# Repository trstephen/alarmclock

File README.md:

# alarmclock
### What is CENG 299?
CENG 299 is a second year project course at the University of Victoria. Students execute the full design cycle to create an alarm clock with mp3 audio playback capabilities. A [STM32F407VG](http://www.st.com/web/catalog/mmc/FM141/SC1169/SS1577/LN11/PF252140) microcontroller is responsible for handling I/O, decoding the mp3 and generating the audio output. A custom-designed PCB filters and amplifies the audio output from the STM and contains the circuitry for driving the 7-segment display and cleaning up button input.

### What's in the repo?
**Schematics**

Detail the four main components of the circuit design:
* I/O
* Audio amplification and filtering
* External button connections
* 7-Segment display controller

The files will open natively in  [KiCad](http://www.kicad-pcb.org/display/KICAD/KiCad+EDA+Software+Suite).

Printable schematics, with some helpful notes, are [here](kicad/schematic.pdf).

*TODO*: Include files for the PCB.

**Code**

A skeleton was provided that handles the USB On-The-Go communication and audio decoding. The bulk of the project code is in:
```
main.c
state_machine.c
buttons.c
clock_display.c
```
The included `.coproj` file will open the project in [CoIDE](http://www.coocox.org/software/coide.php) but the project should work wherever the [GCC-ARM](https://launchpad.net/gcc-arm-embedded) compiler is used.

**Known Issues**

* mp3 playback
  * Only works with 128kb/s encoding
  * Stops playback after ~2min and needs to be hard reset before playback can continue

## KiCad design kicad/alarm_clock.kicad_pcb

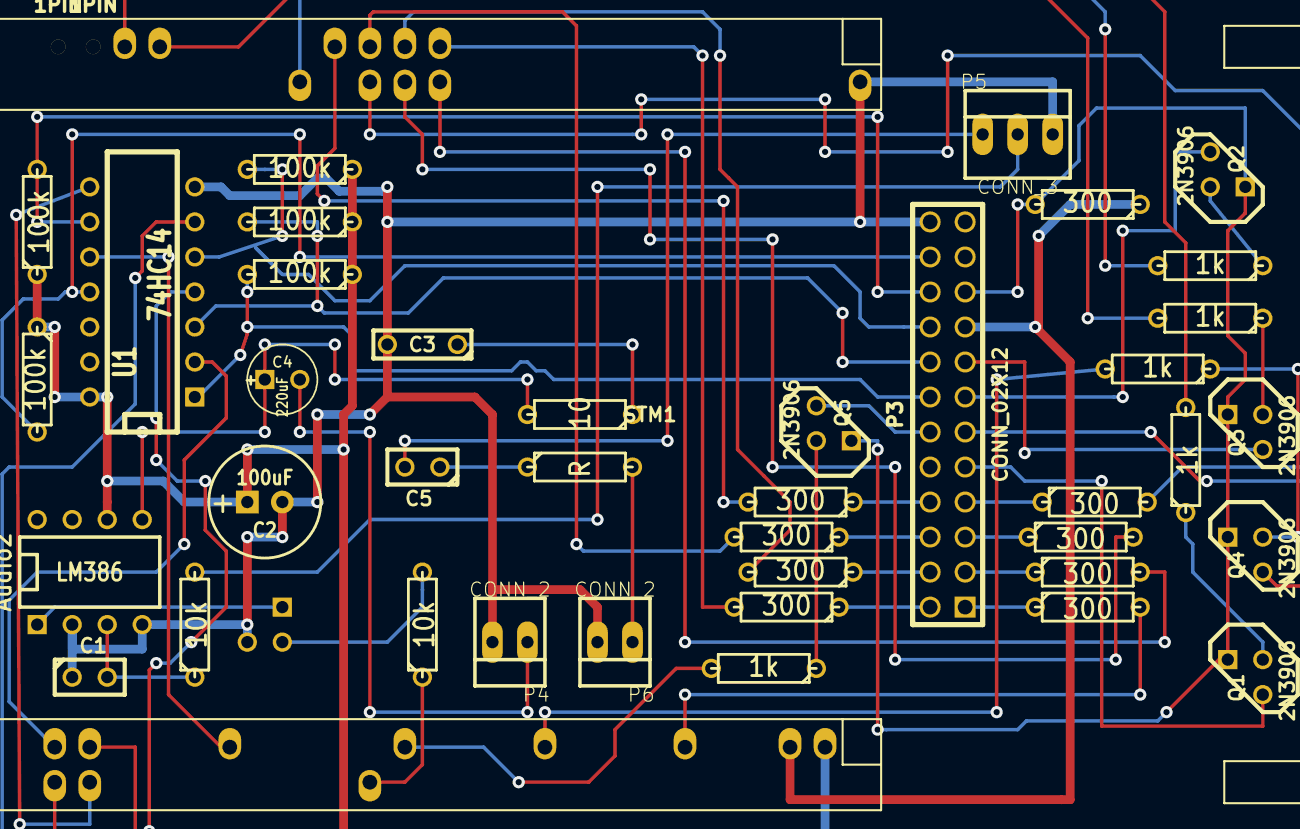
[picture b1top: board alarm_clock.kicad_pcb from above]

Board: 2 copper layers, 43 parts (1 on the bottom side), 56 nets.

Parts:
1PIN, 1PIN#2: P***; 1pin
Audio2: LM386; DIP-8__300
C1: 800pF; C1
C2: 100uF; C1V8
C3: .047uF; C2
C4: 220uF; C1V5
C5: 0.01uF; C1
M1: 2N7000; TO92DGS
P3: CONN_02X12; pin_array_12x2
P4, P6: CONN_2; PINHEAD1-2
P5: CONN_3; PINHEAD1-3
Q1, Q2, Q3, Q4, Q5: 2N3906; TO92-CBE
R1, R2, R4, R5, R6, R7, R8, R9, R10: 300; R3
R3, R20, R21, R22, R23: 1k; R3
R11, R12: 10k; R3
R13: 10; R3
R14, R15, R16, R17, R18: 100k; R3
R19: R; R3
STM1: STM32_F4_DISCOVERY; STM32F4DISC
U1: 74HC14; DIP-14__300

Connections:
3V_205: P3.17, R8.1, STM1.2-5
5V_203: Audio2.6, C2.1, R14.1, R15.1, R16.1, R17.1, R18.1, STM1.2-3, U1.14
AudioIn: C5.1, R19.1
AudioJackGrnd: Audio2.2, Audio2.4, C1.1, C2.2, C3.2, M1.S, P3.24, P4.2, P5.3, P6.2, STM1.1-2, U1.7
AudiojackOut: P6.1, R19.2
DIG_COLON: P3.15, Q3.C
DIG_H01: P3.13, Q2.C
DIG_H10: P3.9, Q1.C
DIG_M01: P3.12, Q5.C
DIG_M10: P3.11, Q4.C
unnamed: Q2.B, R20.1
unnamed: Q5.B, R23.1
unnamed: Q1.B, R3.1
unnamed: Q4.B, R22.1
unnamed: Q3.B, R21.1
unnamed: C3.1, R13.1
unnamed: Audio2.5, C4.1, R13.2
unnamed: M1.G, R12.2
unnamed: Audio2.3, C1.2, R11.1
unnamed: Audio2.1, M1.D
PC6: STM1.2-47, U1.2
PC7: STM1.2-48, U1.4
PC8: STM1.2-45, U1.6
PC9: STM1.2-46, U1.8
PC10: STM1.2-37, U1.10
PD6: R12.1, STM1.2-30
PD7: R23.2, STM1.2-27
PD8: R22.2, STM1.2-19
PD9: R21.2, STM1.1-41
PD10: R20.2, STM1.1-34
PD11: R3.2, STM1.1-43
PE6: R1.2, STM1.2-11
PE7: R2.2, STM1.1-25
PE8: R4.2, STM1.1-26
PE9: R5.2, STM1.1-27
PE10: R6.2, STM1.1-28
PE11: R7.2, STM1.1-29
PE12: R9.2, STM1.1-30
PE13: R10.2, STM1.1-31
PHOTO-: P3.19, Q1.E, Q2.E, Q3.E, Q4.E, Q5.E, R8.2
S1: P3.14, R14.2, U1.1
S2: P3.16, R15.2, U1.3
S3: P3.18, R16.2, U1.5
S4: P3.20, R17.2, U1.9
S5: P3.22, R18.2, U1.11
SEG_A: P3.1, R1.1
SEG_B: P3.2, R2.1
SEG_C: P3.3, R4.1
SEG_D: P3.4, R5.1
SEG_DP: P3.8, R10.1
SEG_E: P3.5, R6.1
SEG_F: P3.6, R7.1
SEG_G: P3.7, R9.1
SPKR+: C4.2, P4.1
VOL+: C5.2, P5.1
VOL_SEL: P5.2, R11.2

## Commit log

2015-06-05 :circus_tent: Added .gitattributes & .gitignore files
2015-06-05 Initial commit
    I think I excluded all the right compiled artifacts? Let's find out!
2015-06-05 The littlest readme
2015-06-07 Proj update before branch
    Updated ignore to exclude some (I think) useless IDE config files.
2015-06-07 clocktest()
    Lights all segments on the clock, one digit at a time. Untested on the
    board! Compiles, but who knows what it does....
2015-06-08 Creation of clock_display
    Extracted GPIO configuration from main into clock_display.
    Test method now lives in clock_display.
    Hooks for new functions are in main but are commented out.
    Untested on the board!
2015-06-09 Interrupt sequence fixed
    Gotta clear the interrupt flag last.
    Files c/p'd from the lab machine; lots of commits of files that are
    unchanged! No more working on the lab machine :(
2015-06-09 Revert "Interrupt sequence fixed"
    This reverts commit e7e204ce43aa066f86588d32e030751ee9580d98.
2015-06-09 Actually fixed interrupt sequence
    Come on, no conflicts :(
2015-06-18 add kicad files
2015-06-19 initial routing
2015-06-19 Drill hole sizes fixed
    Match APCircuits free sizes
    Header holes deleted D:
2015-06-20 Final routing
    Removed some intermediary routing steps, too
2015-06-20 New pcb file
    How did this not get syncd?
2015-06-30 12:12 Display test
    Constant time used for display testing. Only two leads (E6, E7) are
    needed to differentiate the two digits.
2015-06-30 Rough clock test
    Displays minutes : seconds from the RTC
2015-07-09 Add audio enable pin
2015-07-09 Final schematics
    Also includes pdf
2015-07-09 Button stubs
    Added basic button interrupt handler. C10 toggles onboard LED.
2015-07-15 Button struct added
    Mmm, global variables. All over this project.
2015-07-15 Display array
    Condensed all of the constants for the display pins into an array. Makes
    it a bit cleaner? Gets rid of the switch statement for assigning
    display digits from decimal values.
2015-07-18 New button handling *untested*
    Buttons are now checked through polling
2015-07-18 *untested* Function pointers for button presses
    Implementing the long/short button press functions via function pointers
    to functions from the state machine.
    Cleaned up some of the old external interrupt methods for button
    presses.
2015-07-19 Fixed 10s digit time display
2015-07-20 Button debouncing working
2015-07-20 Added ClockDisplay struct
    setting the groundwork for making an extensible clock display. the clock
    display update is a function pointer which will point to the appropriate
    time to display (RTC, alarm, set time)
2015-07-20 12/24 Hr toggle; Blinking colon
2015-07-21 *untested* Button functions refactor
    Button functions can only change the global state and do minor flag
    changes (12/24 hr; incr time). The state machine is responsible for
    changing button functions and display functions.
2015-07-22 Time setting enabled
    Time can be set in 12. or 24h mode.
    Refactoring confirmed safe! State machine is up and running.
2015-07-22 Alarm time setting
    You can set the alarm but it isn't handled or anything.
2015-07-25 *broken* New audio processor
    Supposed to solve a skipping problem with mono tracks. Initial testing
    was negative.
    Attempting to pause or stop audio playback causes skipping.
2015-07-25 Comments!
    So much commenting…
2015-07-30 Corrected audio playback
    It was mainly a sample rate error. The "fix" is to use a 128 kbps mp3
    for playback~
2015-07-30 github noooo
    i am bad with sync conflict :3
2015-08-12 *Fix* Snooze reactivates
    Fixed bug where snooze would trigger once and then not again.
2015-08-12 File tidying
    Moved all the code into its own folder
2015-08-12 Updated readme
    It’s actually helpful now.
2015-08-12 *Fix* Missing IO pins
    Added PA4 to the schematic IO page and fixed PD8, PD10
